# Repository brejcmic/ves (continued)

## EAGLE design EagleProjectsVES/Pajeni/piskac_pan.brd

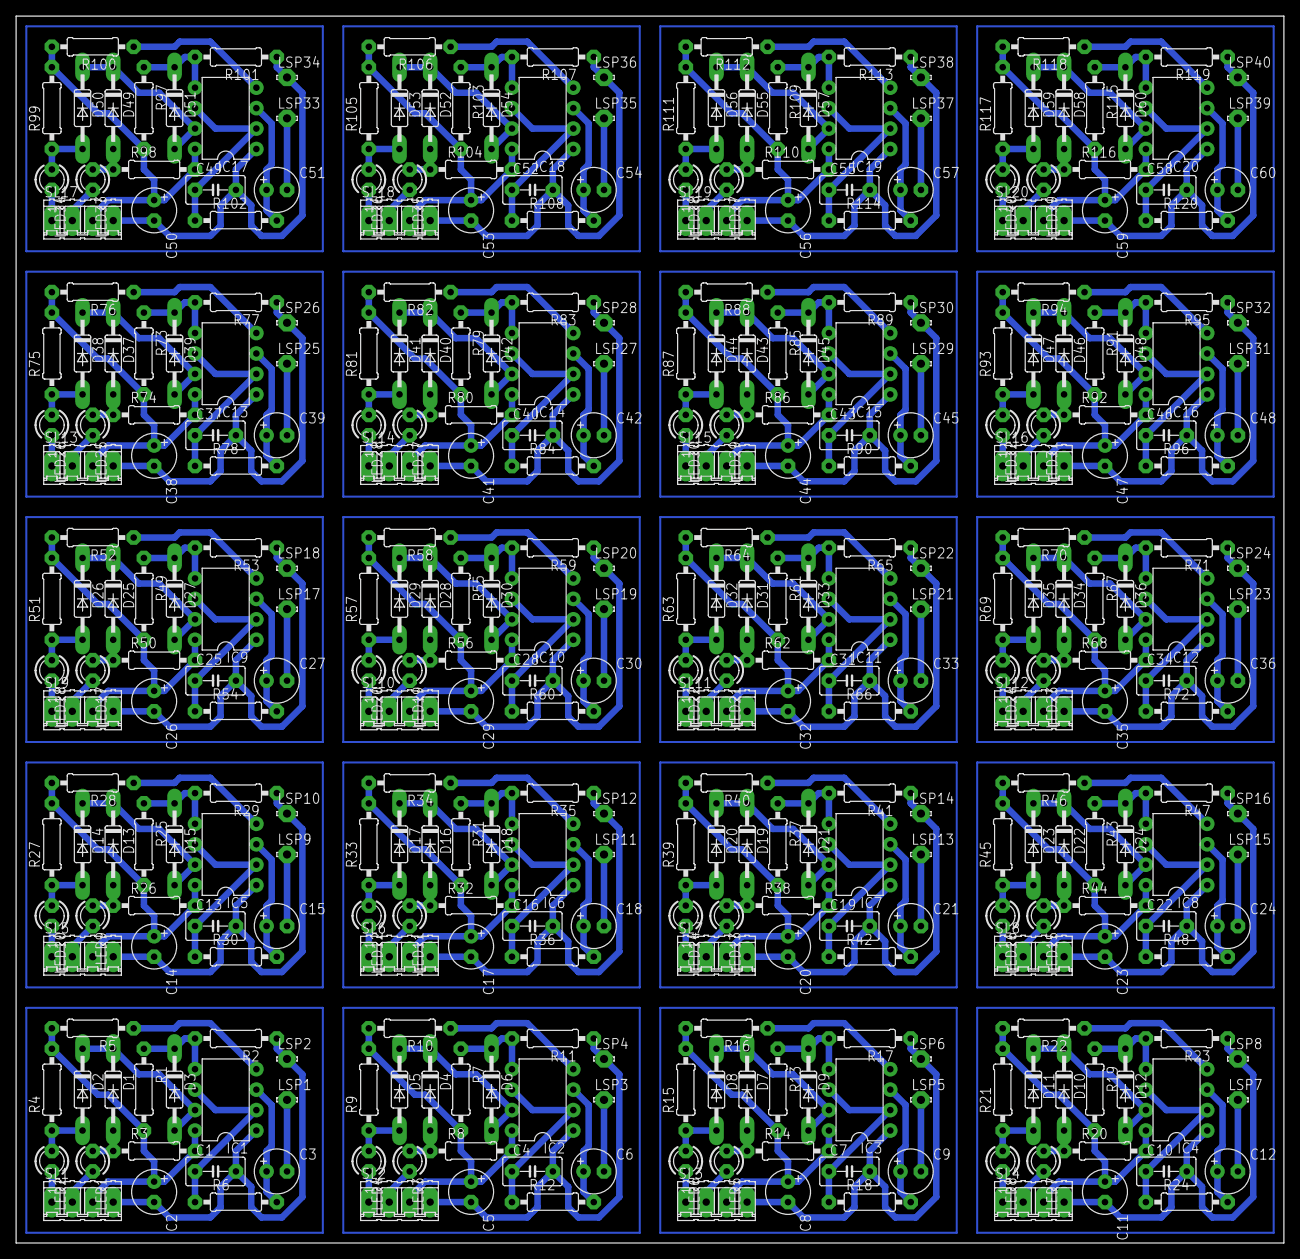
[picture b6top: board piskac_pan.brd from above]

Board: 2 copper layers, 157.5 x 152.4 mm, 361 parts (0 on the bottom side), 240 nets.

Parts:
C1, C4, C7, C10, C13, C16, C19, C22, C25, C28, C31, C34, C37, C40, C43, C46, C49, C52, C55, C58: 12n; C5B3.5
C2, C3, C5, C6, C8, C9, C11, C12, C14, C15, C17, C18, C20, C21, C23, C24, C26, C27, C29, C30, C32, C33, C35, C36, C38, C39, C41, C42, C44, C45, C47, C48, C50, C51, C53, C54, C56, C57, C59, C60: 10u; E2,5-6
D1, D2, D3, D4, D5, D6, D7, D8, D9, D10, D11, D12, D13, D14, D15, D16, D17, D18, D19, D20, D21, D22, D23, D24, D25, D26, D27, D28, D29, D30, D31, D32, D33, D34, D35, D36, D37, D38, D39, D40, D41, D42, D43, D44, D45, D46, D47, D48, D49, D50, D51, D52, D53, D54, D55, D56, D57, D58, D59, D60: 1N4148; DO35-10
DRILEGEND: DRILEGEND
IC1, IC2, IC3, IC4, IC5, IC6, IC7, IC8, IC9, IC10, IC11, IC12, IC13, IC14, IC15, IC16, IC17, IC18, IC19, IC20: NE555N; DIL08
LED1, LED3, LED5, LED7, LED9, LED11, LED13, LED15, LED17, LED19, LED21, LED23, LED25, LED27, LED29, LED31, LED33, LED35, LED37, LED39: RED; LED3MM
LED2, LED4, LED6, LED8, LED10, LED12, LED14, LED16, LED18, LED20, LED22, LED24, LED26, LED28, LED30, LED32, LED34, LED36, LED38, LED40: GREEN; LED3MM
LSP1, LSP2, LSP3, LSP4, LSP5, LSP6, LSP7, LSP8, LSP9, LSP10, LSP11, LSP12, LSP13, LSP14, LSP15, LSP16, LSP17, LSP18, LSP19, LSP20, LSP21, LSP22, LSP23, LSP24, LSP25, LSP26, LSP27, LSP28, LSP29, LSP30, LSP31, LSP32, LSP33, LSP34, LSP35, LSP36, LSP37, LSP38, LSP39, LSP40: LSP10
R1, R7, R13, R19, R25, R31, R37, R43, R49, R55, R61, R67, R73, R79, R85, R91, R97, R103, R109, R115: 750R; 0207/10
R2, R4, R9, R11, R15, R17, R21, R23, R27, R29, R33, R35, R39, R41, R45, R47, R51, R53, R57, R59, R63, R65, R69, R71, R75, R77, R81, R83, R87, R89, R93, R95, R99, R101, R105, R107, R111, R113, R117, R119: 1k5; 0207/10
R3, R5, R8, R10, R14, R16, R20, R22, R26, R28, R32, R34, R38, R40, R44, R46, R50, R52, R56, R58, R62, R64, R68, R70, R74, R76, R80, R82, R86, R88, R92, R94, R98, R100, R104, R106, R110, R112, R116, R118: 3k3; 0207/10
R6, R12, R18, R24, R30, R36, R42, R48, R54, R60, R66, R72, R78, R84, R90, R96, R102, R108, R114, R120: 110k; 0207/10
SL1, SL2, SL3, SL4, SL5, SL6, SL7, SL8, SL9, SL10, SL11, SL12, SL13, SL14, SL15, SL16, SL17, SL18, SL19, SL20: 04P

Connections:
+12V: C2.+, IC1.8, R1.2, R3.2, R4.2, R5.2, SL1.3
+12V1: C5.+, IC2.8, R7.2, R8.2, R9.2, R10.2, SL2.3
+12V2: C8.+, IC3.8, R13.2, R14.2, R15.2, R16.2, SL3.3
+12V3: C11.+, IC4.8, R19.2, R20.2, R21.2, R22.2, SL4.3
+12V4: C14.+, IC5.8, R25.2, R26.2, R27.2, R28.2, SL5.3
+12V5: C17.+, IC6.8, R31.2, R32.2, R33.2, R34.2, SL6.3
+12V6: C20.+, IC7.8, R37.2, R38.2, R39.2, R40.2, SL7.3
+12V7: C23.+, IC8.8, R43.2, R44.2, R45.2, R46.2, SL8.3
+12V8: C26.+, IC9.8, R49.2, R50.2, R51.2, R52.2, SL9.3
+12V9: C29.+, IC10.8, R55.2, R56.2, R57.2, R58.2, SL10.3
+12V10: C32.+, IC11.8, R61.2, R62.2, R63.2, R64.2, SL11.3
+12V11: C35.+, IC12.8, R67.2, R68.2, R69.2, R70.2, SL12.3
+12V12: C38.+, IC13.8, R73.2, R74.2, R75.2, R76.2, SL13.3
+12V13: C41.+, IC14.8, R79.2, R80.2, R81.2, R82.2, SL14.3
+12V14: C44.+, IC15.8, R85.2, R86.2, R87.2, R88.2, SL15.3
+12V15: C47.+, IC16.8, R91.2, R92.2, R93.2, R94.2, SL16.3
+12V16: C50.+, IC17.8, R97.2, R98.2, R99.2, R100.2, SL17.3
+12V17: C53.+, IC18.8, R103.2, R104.2, R105.2, R106.2, SL18.3
+12V18: C56.+, IC19.8, R109.2, R110.2, R111.2, R112.2, SL19.3
+12V19: C59.+, IC20.8, R115.2, R116.2, R117.2, R118.2, SL20.3
GND: C1.2, C2.-, IC1.1, LSP2.MP, R2.1, SL1.4
GND1: C4.2, C5.-, IC2.1, LSP4.MP, R11.1, SL2.4
GND2: C7.2, C8.-, IC3.1, LSP6.MP, R17.1, SL3.4
GND3: C10.2, C11.-, IC4.1, LSP8.MP, R23.1, SL4.4
GND4: C13.2, C14.-, IC5.1, LSP10.MP, R29.1, SL5.4
GND5: C16.2, C17.-, IC6.1, LSP12.MP, R35.1, SL6.4
GND6: C19.2, C20.-, IC7.1, LSP14.MP, R41.1, SL7.4
GND7: C22.2, C23.-, IC8.1, LSP16.MP, R47.1, SL8.4
GND8: C25.2, C26.-, IC9.1, LSP18.MP, R53.1, SL9.4
GND9: C28.2, C29.-, IC10.1, LSP20.MP, R59.1, SL10.4
GND10: C31.2, C32.-, IC11.1, LSP22.MP, R65.1, SL11.4
GND11: C34.2, C35.-, IC12.1, LSP24.MP, R71.1, SL12.4
GND12: C37.2, C38.-, IC13.1, LSP26.MP, R77.1, SL13.4
GND13: C40.2, C41.-, IC14.1, LSP28.MP, R83.1, SL14.4
GND14: C43.2, C44.-, IC15.1, LSP30.MP, R89.1, SL15.4
GND15: C46.2, C47.-, IC16.1, LSP32.MP, R95.1, SL16.4
GND16: C49.2, C50.-, IC17.1, LSP34.MP, R101.1, SL17.4
GND17: C52.2, C53.-, IC18.1, LSP36.MP, R107.1, SL18.4
GND18: C55.2, C56.-, IC19.1, LSP38.MP, R113.1, SL19.4
GND19: C58.2, C59.-, IC20.1, LSP40.MP, R119.1, SL20.4
unnamed: C1.1, IC1.2, IC1.6, R6.1
unnamed: D3.C, IC1.5, R1.1, R2.2
unnamed: C3.-, LSP1.MP
unnamed: IC1.4, R5.1
unnamed: D1.A, LED1.A, R3.1
unnamed: LED1.K, SL1.2
unnamed: D2.A, LED2.A, R4.1
unnamed: C3.+, IC1.3, R6.2
unnamed: D1.C, D2.C, D3.A, IC1.7
unnamed: C6.+, IC2.3, R12.2
unnamed: LED2.K, SL1.1
unnamed: LED3.K, SL2.2
unnamed: LED4.K, SL2.1
unnamed: C4.1, IC2.2, IC2.6, R12.1
unnamed: D4.A, LED3.A, R8.1
unnamed: D5.A, LED4.A, R9.1
unnamed: IC2.4, R10.1
unnamed: D6.C, IC2.5, R7.1, R11.2
unnamed: D4.C, D5.C, D6.A, IC2.7
unnamed: C6.-, LSP3.MP
unnamed: C9.+, IC3.3, R18.2
unnamed: LED5.K, SL3.2
unnamed: LED6.K, SL3.1
unnamed: C7.1, IC3.2, IC3.6, R18.1
unnamed: D7.A, LED5.A, R14.1
unnamed: D8.A, LED6.A, R15.1
unnamed: IC3.4, R16.1
unnamed: D9.C, IC3.5, R13.1, R17.2
unnamed: D7.C, D8.C, D9.A, IC3.7
unnamed: C9.-, LSP5.MP
unnamed: C12.+, IC4.3, R24.2
unnamed: LED7.K, SL4.2
unnamed: LED8.K, SL4.1
unnamed: C10.1, IC4.2, IC4.6, R24.1
unnamed: D10.A, LED7.A, R20.1
unnamed: D11.A, LED8.A, R21.1
unnamed: IC4.4, R22.1
unnamed: D12.C, IC4.5, R19.1, R23.2
unnamed: D10.C, D11.C, D12.A, IC4.7
unnamed: C12.-, LSP7.MP
unnamed: C15.+, IC5.3, R30.2
unnamed: LED9.K, SL5.2
unnamed: LED10.K, SL5.1
unnamed: C13.1, IC5.2, IC5.6, R30.1
unnamed: D13.A, LED9.A, R26.1
unnamed: D14.A, LED10.A, R27.1
unnamed: IC5.4, R28.1
unnamed: D15.C, IC5.5, R25.1, R29.2
unnamed: D13.C, D14.C, D15.A, IC5.7
unnamed: C15.-, LSP9.MP
unnamed: C18.+, IC6.3, R36.2
unnamed: LED11.K, SL6.2
unnamed: LED12.K, SL6.1
unnamed: C16.1, IC6.2, IC6.6, R36.1
unnamed: D16.A, LED11.A, R32.1
unnamed: D17.A, LED12.A, R33.1
unnamed: IC6.4, R34.1
unnamed: D18.C, IC6.5, R31.1, R35.2
unnamed: D16.C, D17.C, D18.A, IC6.7
unnamed: C18.-, LSP11.MP
unnamed: C21.+, IC7.3, R42.2
unnamed: LED13.K, SL7.2
unnamed: LED14.K, SL7.1
unnamed: C19.1, IC7.2, IC7.6, R42.1
unnamed: D19.A, LED13.A, R38.1
unnamed: D20.A, LED14.A, R39.1
unnamed: IC7.4, R40.1
unnamed: D21.C, IC7.5, R37.1, R41.2
unnamed: D19.C, D20.C, D21.A, IC7.7
unnamed: C21.-, LSP13.MP
unnamed: C24.+, IC8.3, R48.2
unnamed: LED15.K, SL8.2
unnamed: LED16.K, SL8.1
unnamed: C22.1, IC8.2, IC8.6, R48.1
unnamed: D22.A, LED15.A, R44.1
unnamed: D23.A, LED16.A, R45.1
unnamed: IC8.4, R46.1
unnamed: D24.C, IC8.5, R43.1, R47.2
unnamed: D22.C, D23.C, D24.A, IC8.7
unnamed: C24.-, LSP15.MP
unnamed: C27.+, IC9.3, R54.2
unnamed: LED17.K, SL9.2
unnamed: LED18.K, SL9.1
unnamed: C25.1, IC9.2, IC9.6, R54.1
unnamed: D25.A, LED17.A, R50.1
unnamed: D26.A, LED18.A, R51.1
unnamed: IC9.4, R52.1
unnamed: D27.C, IC9.5, R49.1, R53.2
unnamed: D25.C, D26.C, D27.A, IC9.7
unnamed: C27.-, LSP17.MP
unnamed: C30.+, IC10.3, R60.2
unnamed: LED19.K, SL10.2
unnamed: LED20.K, SL10.1
unnamed: C28.1, IC10.2, IC10.6, R60.1
unnamed: D28.A, LED19.A, R56.1
unnamed: D29.A, LED20.A, R57.1
unnamed: IC10.4, R58.1
unnamed: D30.C, IC10.5, R55.1, R59.2
unnamed: D28.C, D29.C, D30.A, IC10.7
unnamed: C30.-, LSP19.MP
unnamed: C33.+, IC11.3, R66.2
unnamed: LED21.K, SL11.2
unnamed: LED22.K, SL11.1
unnamed: C31.1, IC11.2, IC11.6, R66.1
unnamed: D31.A, LED21.A, R62.1
unnamed: D32.A, LED22.A, R63.1
unnamed: IC11.4, R64.1
unnamed: D33.C, IC11.5, R61.1, R65.2
unnamed: D31.C, D32.C, D33.A, IC11.7
unnamed: C33.-, LSP21.MP
unnamed: C36.+, IC12.3, R72.2
unnamed: LED23.K, SL12.2
unnamed: LED24.K, SL12.1
unnamed: C34.1, IC12.2, IC12.6, R72.1
unnamed: D34.A, LED23.A, R68.1
unnamed: D35.A, LED24.A, R69.1
unnamed: IC12.4, R70.1
unnamed: D36.C, IC12.5, R67.1, R71.2
unnamed: D34.C, D35.C, D36.A, IC12.7
unnamed: C36.-, LSP23.MP
unnamed: C39.+, IC13.3, R78.2
unnamed: LED25.K, SL13.2
unnamed: LED26.K, SL13.1
unnamed: C37.1, IC13.2, IC13.6, R78.1
unnamed: D37.A, LED25.A, R74.1
unnamed: D38.A, LED26.A, R75.1
unnamed: IC13.4, R76.1
unnamed: D39.C, IC13.5, R73.1, R77.2
unnamed: D37.C, D38.C, D39.A, IC13.7
unnamed: C39.-, LSP25.MP
unnamed: C42.+, IC14.3, R84.2
unnamed: LED27.K, SL14.2
unnamed: LED28.K, SL14.1
unnamed: C40.1, IC14.2, IC14.6, R84.1
unnamed: D40.A, LED27.A, R80.1
unnamed: D41.A, LED28.A, R81.1
unnamed: IC14.4, R82.1
unnamed: D42.C, IC14.5, R79.1, R83.2
unnamed: D40.C, D41.C, D42.A, IC14.7
unnamed: C42.-, LSP27.MP
unnamed: C45.+, IC15.3, R90.2
unnamed: LED29.K, SL15.2
unnamed: LED30.K, SL15.1
unnamed: C43.1, IC15.2, IC15.6, R90.1
unnamed: D43.A, LED29.A, R86.1
unnamed: D44.A, LED30.A, R87.1
unnamed: IC15.4, R88.1
unnamed: D45.C, IC15.5, R85.1, R89.2
unnamed: D43.C, D44.C, D45.A, IC15.7
unnamed: C45.-, LSP29.MP
unnamed: C48.+, IC16.3, R96.2
unnamed: LED31.K, SL16.2
unnamed: LED32.K, SL16.1
unnamed: C46.1, IC16.2, IC16.6, R96.1
unnamed: D46.A, LED31.A, R92.1
unnamed: D47.A, LED32.A, R93.1
unnamed: IC16.4, R94.1
unnamed: D48.C, IC16.5, R91.1, R95.2
unnamed: D46.C, D47.C, D48.A, IC16.7
unnamed: C48.-, LSP31.MP
unnamed: C51.+, IC17.3, R102.2
unnamed: LED33.K, SL17.2
unnamed: LED34.K, SL17.1
unnamed: C49.1, IC17.2, IC17.6, R102.1
unnamed: D49.A, LED33.A, R98.1
unnamed: D50.A, LED34.A, R99.1
unnamed: IC17.4, R100.1
unnamed: D51.C, IC17.5, R97.1, R101.2
unnamed: D49.C, D50.C, D51.A, IC17.7
unnamed: C51.-, LSP33.MP
unnamed: C54.+, IC18.3, R108.2
unnamed: LED35.K, SL18.2
unnamed: LED36.K, SL18.1
unnamed: C52.1, IC18.2, IC18.6, R108.1
unnamed: D52.A, LED35.A, R104.1
unnamed: D53.A, LED36.A, R105.1
unnamed: IC18.4, R106.1
unnamed: D54.C, IC18.5, R103.1, R107.2
unnamed: D52.C, D53.C, D54.A, IC18.7
unnamed: C54.-, LSP35.MP
unnamed: C57.+, IC19.3, R114.2
unnamed: LED37.K, SL19.2
unnamed: LED38.K, SL19.1
unnamed: C55.1, IC19.2, IC19.6, R114.1
unnamed: D55.A, LED37.A, R110.1
unnamed: D56.A, LED38.A, R111.1
unnamed: IC19.4, R112.1
unnamed: D57.C, IC19.5, R109.1, R113.2
unnamed: D55.C, D56.C, D57.A, IC19.7
unnamed: C57.-, LSP37.MP
unnamed: C60.+, IC20.3, R120.2
unnamed: LED39.K, SL20.2
unnamed: LED40.K, SL20.1
unnamed: C58.1, IC20.2, IC20.6, R120.1
unnamed: D58.A, LED39.A, R116.1
unnamed: D59.A, LED40.A, R117.1
unnamed: IC20.4, R118.1
unnamed: D60.C, IC20.5, R115.1, R119.2
unnamed: D58.C, D59.C, D60.A, IC20.7
unnamed: C60.-, LSP39.MP

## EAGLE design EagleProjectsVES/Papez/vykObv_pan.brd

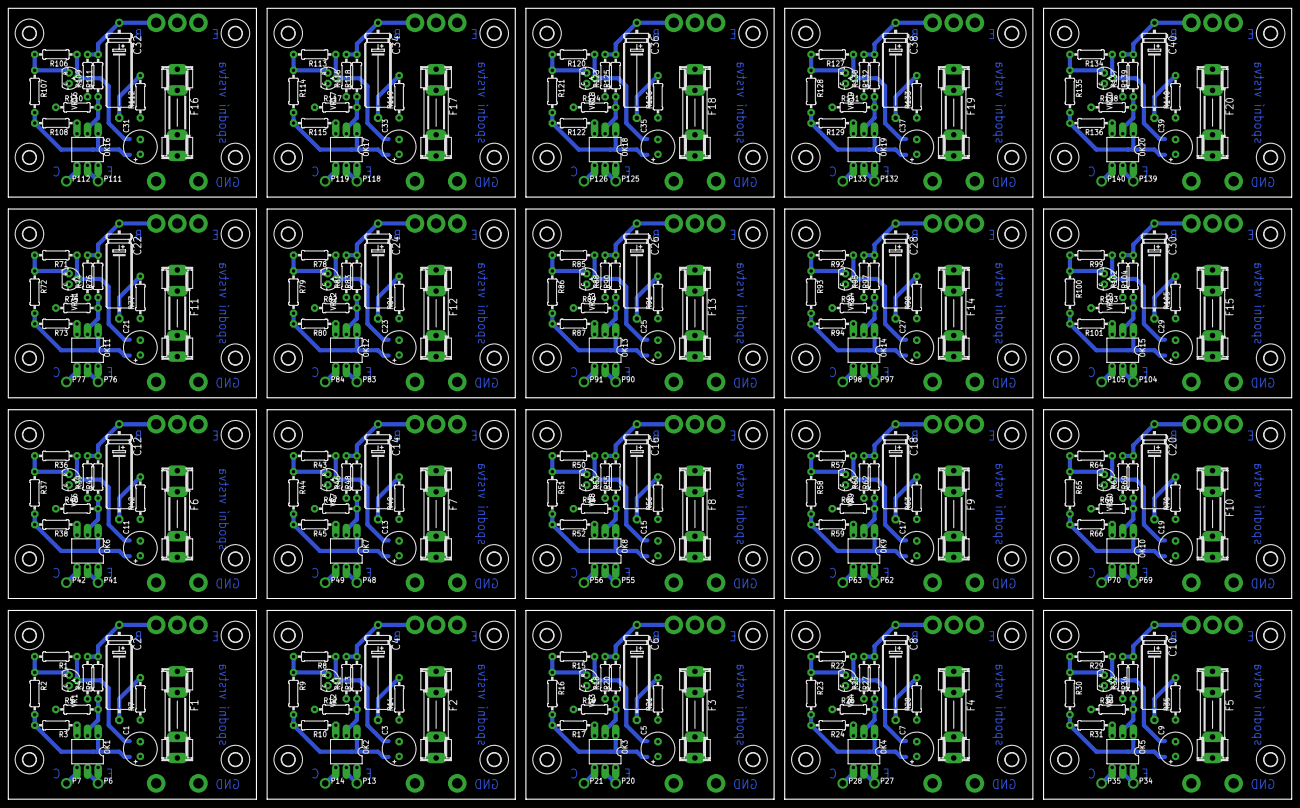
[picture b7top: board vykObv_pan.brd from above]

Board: 2 copper layers, 308.6 x 190.2 mm, 460 parts (0 on the bottom side), 200 nets.

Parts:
C1, C3, C5, C7, C9, C11, C13, C15, C17, C19, C21, C23, C25, C27, C29, C31, C33, C35, C37, C39: 220M; E3,5-8
C2, C4, C6, C8, C10, C12, C14, C16, C18, C20, C22, C24, C26, C28, C30, C32, C34, C36, C38, C40: 10M; E22-6
F1, F2, F3, F4, F5, F6, F7, F8, F9, F10, F11, F12, F13, F14, F15, F16, F17, F18, F19, F20: FUSESHK20L; SHK20L
OK1, OK2, OK3, OK4, OK5, OK6, OK7, OK8, OK9, OK10, OK11, OK12, OK13, OK14, OK15, OK16, OK17, OK18, OK19, OK20: 4N35; DIL06
P1, P8, P15, P22, P29, P36, P43, P50, P57, P64, P71, P78, P85, P92, P99, P106, P113, P120, P127, P134: VCC; PAD2.5MM
P2, P9, P16, P23, P30, P37, P44, P51, P58, P65, P72, P79, P86, P93, P100, P107, P114, P121, P128, P135: GND; PAD2.5MM
P3, P10, P17, P24, P31, P38, P45, P52, P59, P66, P73, P80, P87, P94, P101, P108, P115, P122, P129, P136: B; PAD2.5MM
P4, P11, P18, P25, P32, P39, P46, P53, P60, P67, P74, P81, P88, P95, P102, P109, P116, P123, P130, P137: C; PAD2.5MM
P5, P12, P19, P26, P33, P40, P47, P54, P61, P68, P75, P82, P89, P96, P103, P110, P117, P124, P131, P138: E; PAD2.5MM
P6, P13, P20, P27, P34, P41, P48, P55, P62, P69, P76, P83, P90, P97, P104, P111, P118, P125, P132, P139: X4; PAD1.6MM
P7, P14, P21, P28, P35, P42, P49, P56, P63, P70, P77, P84, P91, P98, P105, P112, P119, P126, P133, P140: X3; PAD1.6MM
R1, R8, R15, R22, R29, R36, R43, R50, R57, R64, R71, R78, R85, R92, R99, R106, R113, R120, R127, R134: 2k2; 0207/10
R2, R9, R16, R23, R30, R37, R44, R51, R58, R65, R72, R79, R86, R93, R100, R107, R114, R121, R128, R135: 1k27; 0207/10
R3, R10, R17, R24, R31, R38, R45, R52, R59, R66, R73, R80, R87, R94, R101, R108, R115, R122, R129, R136: 1k8; 0207/10
R4, R11, R18, R25, R32, R39, R46, R53, R60, R67, R74, R81, R88, R95, R102, R109, R116, R123, R130, R137: 30R; 0207/10
R5, R6, R12, R13, R19, R20, R26, R27, R33, R34, R40, R41, R47, R48, R54, R55, R61, R62, R68, R69, R75, R76, R82, R83, R89, R90, R96, R97, R103, R104, R110, R111, R117, R118, R124, R125, R131, R132, R138, R139: 665R; 0207/10
R7, R14, R21, R28, R35, R42, R49, R56, R63, R70, R77, R84, R91, R98, R105, R112, R119, R126, R133, R140: 3R9; 0207/10
U$1, U$2, U$3, U$4, U$5, U$6, U$7, U$8, U$9, U$10, U$11, U$12, U$13, U$14, U$15, U$16, U$17, U$18, U$19, U$20, U$21, U$22, U$23, U$24, U$25, U$26, U$27, U$28, U$29, U$30, U$31, U$32, U$33, U$34, U$35, U$36, U$37, U$38, U$39, U$40, U$41, U$42, U$43, U$44, U$45, U$46, U$47, U$48, U$49, U$50, U$51, U$52, U$53, U$54, U$55, U$56, U$57, U$58, U$59, U$60, U$61, U$62, U$63, U$64, U$65, U$66, U$67, U$68, U$69, U$70, U$71, U$72, U$73, U$74, U$75, U$76, U$77, U$78, U$79, U$80: 3,2
VR1, VR2, VR3, VR4, VR5, VR6, VR7, VR8, VR9, VR10, VR11, VR12, VR13, VR14, VR15, VR16, VR17, VR18, VR19, VR20: TO92-CLP

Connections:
EMIT: F1.1A, F1.1B, P5.P$1
EMIT1: F2.1A, F2.1B, P12.P$1
EMIT2: F3.1A, F3.1B, P19.P$1
EMIT3: F4.1A, F4.1B, P26.P$1
EMIT4: F5.1A, F5.1B, P33.P$1
EMIT5: F6.1A, F6.1B, P40.P$1
EMIT6: F7.1A, F7.1B, P47.P$1
EMIT7: F8.1A, F8.1B, P54.P$1
EMIT8: F9.1A, F9.1B, P61.P$1
EMIT9: F10.1A, F10.1B, P68.P$1
EMIT10: F11.1A, F11.1B, P75.P$1
EMIT11: F12.1A, F12.1B, P82.P$1
EMIT12: F13.1A, F13.1B, P89.P$1
EMIT13: F14.1A, F14.1B, P96.P$1
EMIT14: F15.1A, F15.1B, P103.P$1
EMIT15: F16.1A, F16.1B, P110.P$1
EMIT16: F17.1A, F17.1B, P117.P$1
EMIT17: F18.1A, F18.1B, P124.P$1
EMIT18: F19.1A, F19.1B, P131.P$1
EMIT19: F20.1A, F20.1B, P138.P$1
GND: C1.-, P2.P$1, P4.P$1, R1.1, R7.1, VR1.A
GND1: C3.-, P9.P$1, P11.P$1, R8.1, R14.1, VR2.A
GND2: C5.-, P16.P$1, P18.P$1, R15.1, R21.1, VR3.A
GND3: C7.-, P23.P$1, P25.P$1, R22.1, R28.1, VR4.A
GND4: C9.-, P30.P$1, P32.P$1, R29.1, R35.1, VR5.A
GND5: C11.-, P37.P$1, P39.P$1, R36.1, R42.1, VR6.A
GND6: C13.-, P44.P$1, P46.P$1, R43.1, R49.1, VR7.A
GND7: C15.-, P51.P$1, P53.P$1, R50.1, R56.1, VR8.A
GND8: C17.-, P58.P$1, P60.P$1, R57.1, R63.1, VR9.A
GND9: C19.-, P65.P$1, P67.P$1, R64.1, R70.1, VR10.A
GND10: C21.-, P72.P$1, P74.P$1, R71.1, R77.1, VR11.A
GND11: C23.-, P79.P$1, P81.P$1, R78.1, R84.1, VR12.A
GND12: C25.-, P86.P$1, P88.P$1, R85.1, R91.1, VR13.A
GND13: C27.-, P93.P$1, P95.P$1, R92.1, R98.1, VR14.A
GND14: C29.-, P100.P$1, P102.P$1, R99.1, R105.1, VR15.A
GND15: C31.-, P107.P$1, P109.P$1, R106.1, R112.1, VR16.A
GND16: C33.-, P114.P$1, P116.P$1, R113.1, R119.1, VR17.A
GND17: C35.-, P121.P$1, P123.P$1, R120.1, R126.1, VR18.A
GND18: C37.-, P128.P$1, P130.P$1, R127.1, R133.1, VR19.A
GND19: C39.-, P135.P$1, P137.P$1, R134.1, R140.1, VR20.A
unnamed: OK2.2, R12.2, R13.1
unnamed: C4.+, P10.P$1, R11.2, R13.2
unnamed: R10.1, R11.1, R12.1, VR2.C
unnamed: OK2.4, P14.P$1
unnamed: OK1.2, R5.2, R6.1
unnamed: C2.+, P3.P$1, R4.2, R6.2
unnamed: R3.1, R4.1, R5.1, VR1.C
unnamed: OK1.4, P7.P$1
unnamed: OK1.5, P6.P$1
unnamed: OK2.5, P13.P$1
unnamed: R1.2, R2.1, VR1.R
unnamed: R8.2, R9.1, VR2.R
unnamed: C2.-, R7.2
unnamed: C4.-, R14.2
unnamed: OK3.2, R19.2, R20.1
unnamed: C6.+, P17.P$1, R18.2, R20.2
unnamed: R17.1, R18.1, R19.1, VR3.C
unnamed: OK3.4, P21.P$1
unnamed: OK3.5, P20.P$1
unnamed: R15.2, R16.1, VR3.R
unnamed: C6.-, R21.2
unnamed: OK4.2, R26.2, R27.1
unnamed: C8.+, P24.P$1, R25.2, R27.2
unnamed: R24.1, R25.1, R26.1, VR4.C
unnamed: OK4.4, P28.P$1
unnamed: OK4.5, P27.P$1
unnamed: R22.2, R23.1, VR4.R
unnamed: C8.-, R28.2
unnamed: OK5.2, R33.2, R34.1
unnamed: C10.+, P31.P$1, R32.2, R34.2
unnamed: R31.1, R32.1, R33.1, VR5.C
unnamed: OK5.4, P35.P$1
unnamed: OK5.5, P34.P$1
unnamed: R29.2, R30.1, VR5.R
unnamed: C10.-, R35.2
unnamed: OK6.2, R40.2, R41.1
unnamed: C12.+, P38.P$1, R39.2, R41.2
unnamed: R38.1, R39.1, R40.1, VR6.C
unnamed: OK6.4, P42.P$1
unnamed: OK6.5, P41.P$1
unnamed: R36.2, R37.1, VR6.R
unnamed: C12.-, R42.2
unnamed: OK7.2, R47.2, R48.1
unnamed: C14.+, P45.P$1, R46.2, R48.2
unnamed: R45.1, R46.1, R47.1, VR7.C
unnamed: OK7.4, P49.P$1
unnamed: OK7.5, P48.P$1
unnamed: R43.2, R44.1, VR7.R
unnamed: C14.-, R49.2
unnamed: OK8.2, R54.2, R55.1
unnamed: C16.+, P52.P$1, R53.2, R55.2
unnamed: R52.1, R53.1, R54.1, VR8.C
unnamed: OK8.4, P56.P$1
unnamed: OK8.5, P55.P$1
unnamed: R50.2, R51.1, VR8.R
unnamed: C16.-, R56.2
unnamed: OK9.2, R61.2, R62.1
unnamed: C18.+, P59.P$1, R60.2, R62.2
unnamed: R59.1, R60.1, R61.1, VR9.C
unnamed: OK9.4, P63.P$1
unnamed: OK9.5, P62.P$1
unnamed: R57.2, R58.1, VR9.R
unnamed: C18.-, R63.2
unnamed: OK10.2, R68.2, R69.1
unnamed: C20.+, P66.P$1, R67.2, R69.2
unnamed: R66.1, R67.1, R68.1, VR10.C
unnamed: OK10.4, P70.P$1
unnamed: OK10.5, P69.P$1
unnamed: R64.2, R65.1, VR10.R
unnamed: C20.-, R70.2
unnamed: OK11.2, R75.2, R76.1
unnamed: C22.+, P73.P$1, R74.2, R76.2
unnamed: R73.1, R74.1, R75.1, VR11.C
unnamed: OK11.4, P77.P$1
unnamed: OK11.5, P76.P$1
unnamed: R71.2, R72.1, VR11.R
unnamed: C22.-, R77.2
unnamed: OK12.2, R82.2, R83.1
unnamed: C24.+, P80.P$1, R81.2, R83.2
unnamed: R80.1, R81.1, R82.1, VR12.C
unnamed: OK12.4, P84.P$1
unnamed: OK12.5, P83.P$1
unnamed: R78.2, R79.1, VR12.R
unnamed: C24.-, R84.2
unnamed: OK13.2, R89.2, R90.1
unnamed: C26.+, P87.P$1, R88.2, R90.2
unnamed: R87.1, R88.1, R89.1, VR13.C
unnamed: OK13.4, P91.P$1
unnamed: OK13.5, P90.P$1
unnamed: R85.2, R86.1, VR13.R
unnamed: C26.-, R91.2
unnamed: OK14.2, R96.2, R97.1
unnamed: C28.+, P94.P$1, R95.2, R97.2
unnamed: R94.1, R95.1, R96.1, VR14.C
unnamed: OK14.4, P98.P$1
unnamed: OK14.5, P97.P$1
unnamed: R92.2, R93.1, VR14.R
unnamed: C28.-, R98.2
unnamed: OK15.2, R103.2, R104.1
unnamed: C30.+, P101.P$1, R102.2, R104.2
unnamed: R101.1, R102.1, R103.1, VR15.C
unnamed: OK15.4, P105.P$1
unnamed: OK15.5, P104.P$1
unnamed: R99.2, R100.1, VR15.R
unnamed: C30.-, R105.2
unnamed: OK16.2, R110.2, R111.1
unnamed: C32.+, P108.P$1, R109.2, R111.2
unnamed: R108.1, R109.1, R110.1, VR16.C
unnamed: OK16.4, P112.P$1
unnamed: OK16.5, P111.P$1
unnamed: R106.2, R107.1, VR16.R
unnamed: C32.-, R112.2
unnamed: OK17.2, R117.2, R118.1
unnamed: C34.+, P115.P$1, R116.2, R118.2
unnamed: R115.1, R116.1, R117.1, VR17.C
unnamed: OK17.4, P119.P$1
unnamed: OK17.5, P118.P$1
unnamed: R113.2, R114.1, VR17.R
unnamed: C34.-, R119.2
unnamed: OK18.2, R124.2, R125.1
unnamed: C36.+, P122.P$1, R123.2, R125.2
unnamed: R122.1, R123.1, R124.1, VR18.C
unnamed: OK18.4, P126.P$1
unnamed: OK18.5, P125.P$1
unnamed: R120.2, R121.1, VR18.R
unnamed: C36.-, R126.2
unnamed: OK19.2, R131.2, R132.1
unnamed: C38.+, P129.P$1, R130.2, R132.2
unnamed: R129.1, R130.1, R131.1, VR19.C
unnamed: OK19.4, P133.P$1
unnamed: OK19.5, P132.P$1
unnamed: R127.2, R128.1, VR19.R
unnamed: C38.-, R133.2
unnamed: OK20.2, R138.2, R139.1
unnamed: C40.+, P136.P$1, R137.2, R139.2
unnamed: R136.1, R137.1, R138.1, VR20.C
unnamed: OK20.4, P140.P$1
unnamed: OK20.5, P139.P$1
unnamed: R134.2, R135.1, VR20.R
unnamed: C40.-, R140.2
VDD: C1.+, F1.2A, F1.2B, OK1.1, P1.P$1, R2.2, R3.2
VDD1: C3.+, F2.2A, F2.2B, OK2.1, P8.P$1, R9.2, R10.2
VDD2: C5.+, F3.2A, F3.2B, OK3.1, P15.P$1, R16.2, R17.2
VDD3: C7.+, F4.2A, F4.2B, OK4.1, P22.P$1, R23.2, R24.2
VDD4: C9.+, F5.2A, F5.2B, OK5.1, P29.P$1, R30.2, R31.2
VDD5: C11.+, F6.2A, F6.2B, OK6.1, P36.P$1, R37.2, R38.2
VDD6: C13.+, F7.2A, F7.2B, OK7.1, P43.P$1, R44.2, R45.2
VDD7: C15.+, F8.2A, F8.2B, OK8.1, P50.P$1, R51.2, R52.2
VDD8: C17.+, F9.2A, F9.2B, OK9.1, P57.P$1, R58.2, R59.2
VDD9: C19.+, F10.2A, F10.2B, OK10.1, P64.P$1, R65.2, R66.2
VDD10: C21.+, F11.2A, F11.2B, OK11.1, P71.P$1, R72.2, R73.2
VDD11: C23.+, F12.2A, F12.2B, OK12.1, P78.P$1, R79.2, R80.2
VDD12: C25.+, F13.2A, F13.2B, OK13.1, P85.P$1, R86.2, R87.2
VDD13: C27.+, F14.2A, F14.2B, OK14.1, P92.P$1, R93.2, R94.2
VDD14: C29.+, F15.2A, F15.2B, OK15.1, P99.P$1, R100.2, R101.2
VDD15: C31.+, F16.2A, F16.2B, OK16.1, P106.P$1, R107.2, R108.2
VDD16: C33.+, F17.2A, F17.2B, OK17.1, P113.P$1, R114.2, R115.2
VDD17: C35.+, F18.2A, F18.2B, OK18.1, P120.P$1, R121.2, R122.2
VDD18: C37.+, F19.2A, F19.2B, OK19.1, P127.P$1, R128.2, R129.2
VDD19: C39.+, F20.2A, F20.2B, OK20.1, P134.P$1, R135.2, R136.2
